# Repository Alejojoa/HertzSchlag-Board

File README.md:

# HertzSchlag - Mini Sumo Board
The HertzSchlag is a PCB designed for Mini Sumo Robots.

## Features :
- Dedicated Servo Pin with PWM control
- Dedicated Start Module pin

- Capability to connect up to 10 sensors (2 analog GPIO, 4 digital GPIO and 4 analog and digital GPIO)
- Mini 360 Step Down
- Two programmable buttons
- XT30 connector and JST(2.54 header pin 1x02)
- On/Off switch
- M2 mounting holes for secure mounting

## Highly Inspired By Tenn Board From DENJU DIVISION :
https://github.com/DENJU-DIVISION/Tenn-PCB/tree/main

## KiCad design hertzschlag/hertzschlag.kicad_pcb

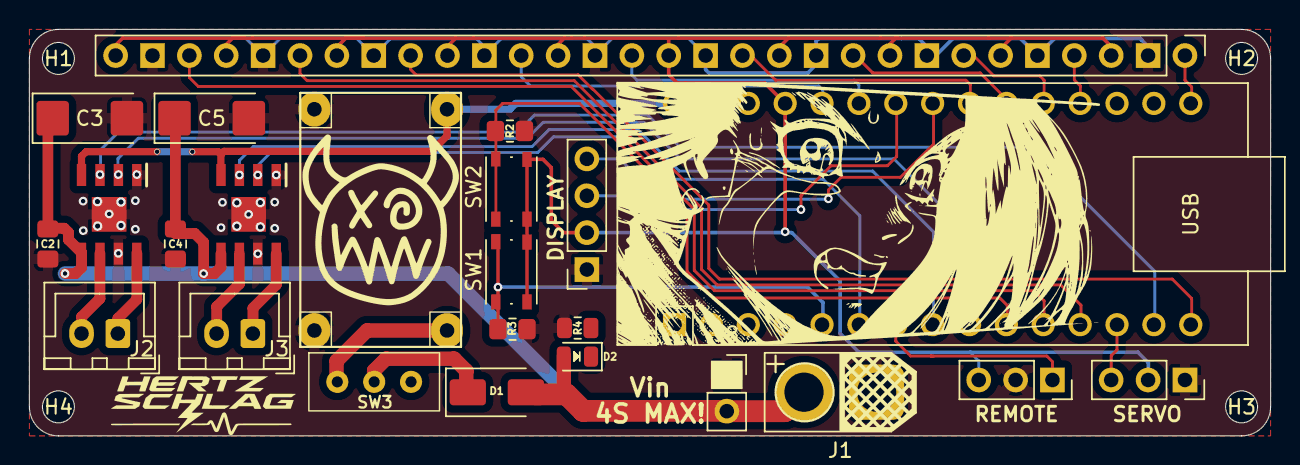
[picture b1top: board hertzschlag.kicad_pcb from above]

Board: 2 copper layers, 85.5 x 28.0 mm, 28 parts (0 on the bottom side), 31 nets.

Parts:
A2: Arduino_Nano_v3.x; Arduino_Nano
C2, C4: 100nF; C_0805_2012Metric_Pad1.18x1.45mm_HandSolder
C3, C5: 47uF; CP_EIA-6032-15_Kemet-U_HandSolder
D1: M7; D_SMA
D2: LED; LED_0805_2012Metric
DISPLAY: Conn_01x04_Female; PinSocket_1x04_P2.54mm_Vertical
H1, H2, H3, H4: MountingHole; MountingHole_2.2mm_M2_ISO7380
IC1, IC2: TB67H450FNG,EL; SOIC127P600X175-9N
J1: TB_1X2; AMASS_XT30U-F_1x02_P5.0mm_Vertical
J2: MotorA; JST_XH_B2B-XH-A_1x02_P2.50mm_Vertical
J3: MotorB; JST_XH_B2B-XH-A_1x02_P2.50mm_Vertical
J4: Conn_01x30_Pin; PinHeader_1x30_P2.54mm_Vertical
J8: Extra; PinSocket_1x02_P2.54mm_Vertical
R2, R3: R; R_0805_2012Metric_Pad1.20x1.40mm_HandSolder
R4: 2.7K; R_0805_2012Metric
REMOTE: Conn_01x03_Male; PinSocket_1x03_P2.54mm_Vertical
SERVO: Conn_01x03_Male; PinSocket_1x03_P2.54mm_Vertical
SW1, SW2: SW_Push; SW_Push_1P1T_NO_Vertical_Wuerth_434133025816
SW3: SW_Push; SW_Slide-03_P2.54_L9_W4_H7
U3: Mini360; Mini360_step-down

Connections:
+5V: A2.27 (+5V), DISPLAY.2, J4.3, J4.6, J4.9, J4.12, J4.15, J4.18, J4.21, J4.24, J4.27, J4.30, REMOTE.3, SERVO.2, SW1.2, SW2.2
/BTN1: A2.5 (D2), R3.2, SW1.1
/BTN2: A2.10 (D7), R2.2, SW2.1
/IN_A1: A2.14 (D11), IC1.3 (IN1)
/IN_A2: A2.9 (D6), IC1.2 (IN2)
/IN_B1: A2.8 (D5), IC2.3 (IN1)
/IN_B2: A2.6 (D3), IC2.2 (IN2)
/MSJS: A2.7 (D4), REMOTE.1
/OUT_A1: IC1.6 (OUT1), J2.2
/OUT_A2: IC1.8 (OUT2), J2.1
/OUT_B1: IC2.6 (OUT1), J3.2
/OUT_B2: IC2.8 (OUT2), J3.1
/SCL: A2.24 (A5), DISPLAY.3
/SDA: A2.23 (A4), DISPLAY.4
/SENSOR0: A2.11 (D8), J4.28
/SENSOR1: A2.12 (D9), J4.25
/SENSOR2: A2.15 (D12), J4.22
/SENSOR3: A2.16 (D13), J4.1
/SENSOR4: A2.19 (A0), J4.4
/SENSOR5: A2.20 (A1), J4.7
/SENSOR6: A2.21 (A2), J4.10
/SENSOR7: A2.22 (A3), J4.13
/SENSOR8: A2.25 (A6), J4.16
/SENSOR9: A2.26 (A7), J4.19
/Servo: A2.13 (D10), SERVO.3
/VM: C2.1, C3.1, C4.1, C5.1, D1.2 (A), D2.2 (A), IC1.5 (VM), IC2.5 (VM), J1.2, J8.2
GND: A2.4 (GND), A2.29 (GND), C2.2, C3.2, C4.2, C5.2, DISPLAY.1, IC1.1 (GND), IC1.7 (RS), IC1.9 (EP), IC2.1 (GND), IC2.7 (RS), IC2.9 (EP), J1.1, J4.2, J4.5, J4.8, J4.11, J4.14, J4.17, J4.20, J4.23, J4.26, J4.29, J8.1, R2.1, R3.1, R4.2, REMOTE.2, SERVO.1, U3.2 (GND)
unnamed: D1.1 (K), SW3.2
unnamed: D2.1 (K), R4.1
unnamed: SW3.1, U3.1 (IN)
VCC: A2.30 (VIN), IC1.4 (VREF), IC2.4 (VREF), U3.3 (OUT)

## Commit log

2025-09-08 Rename README to README.md
2025-09-09 Create LICENSE
2025-09-12 Changes on PCB.
    Changes to Footprints, Routing, Alignment.
    And no more falling alita on the front Silk screen (sad).
2025-10-05 Updated PCB design
    Changes to XT30 Connector and routing.
2025-10-05 Added PCB directory again
2025-10-05 PCBWAY files
2025-10-08 Update README.md
    Added Last Screenshot images, and updated README content
2025-10-08 Delete hertzschlag/pcbway_production/2025-10-05-16-16-27 directory
    Old Files
2025-10-08 Delete hertzschlag directory
    OLD FILES
2025-10-08 PCB and PCBWAY FILES
    Added Last PCB Changes and PCBWAY fabrication files
2025-10-14 PCB and production
